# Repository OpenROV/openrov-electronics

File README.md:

<br>

<div align = center>

# OpenROV

***DIY Telerobotics*** for ***Underwater Exploration*** *&* ***Adventure*** *.*

<br>
<br>

[![Button Website]][Website]   
[![Button Forum]][Forum]   
[![Button BOM]][BOM]   
[![Button Hardware]][Hardware]

</div>

<br>
<br>

## Contents

This repository contains all files related<br>
to our **OpenROV DIY Kits**, these include <br>
`Schematics`, `Gerbers`, `Diagrams`, `..`

<br>
<br>

## Releases

<br>

-   **[`2.6`]**  |  **[`2.7`]**  |  **[`2.8`]**

    All-in-one power and control board that <br>
    has a Arduino based  `Atmega 2560`  board.
    
    Tons of I/O and designed to <br>
    fit the  `BeagleBone Black` .

    <br>

-   **[`2.5`]**

    All-in-one power & control board that has <br>
    a Arduino based  `Atmega 2560`  board.
    
    Tons of I/O and designed to fit both <br>
    `BeagleBone`  &  `BeagleBone Black` .

    <br>

-   **[`2.3`]**  |  **[`2.4`]**

    All-in-one power & control board <br>
    based around the  `Atmega 328` .

<br>

<!----------------------------------------------------------------------------->

[Hardware]: https://github.com/OpenROV/openrov-hardware
[Website]: http://openrov.com/
[Forum]: https://forum.openrov.com/
[BOM]: https://docs.google.com/spreadsheet/ccc?key=0Avf6fUwp9B3kdF9YQWxBTnZjZEVGZVQwY25EbnVyREE&usp=sharing

[`2.3`]: ./OpenROV%20BeagleBone%20Cape%20Rev%20A1%20v2.3%20v2.4
[`2.4`]: ./OpenROV%20BeagleBone%20Cape%20Rev%20A1%20v2.3%20v2.4
[`2.8`]: ./OpenROV%20Controller%202.8%20Final%20Data%20Pkg
[`2.7`]: ./OpenROV%20Controller%202.7%20Final%20Data%20Pkg
[`2.5`]: ./OpenROV%20Controller%202.5B
[`2.6`]: ./OpenROV%20Controller%202.6

<!---------------------------------[ Buttons ]--------------------------------->

[Button Hardware]: https://img.shields.io/badge/Hardware-81B441?style=for-the-badge&logoColor=white&logo=GodotEngine
[Button Website]: https://img.shields.io/badge/Website-1293D8?style=for-the-badge&logoColor=white&logo=GoogleChrome
[Button Forum]: https://img.shields.io/badge/Forum-782A90?style=for-the-badge&logoColor=white&logo=ElasticStack
[Button BOM]: https://img.shields.io/badge/Bill_Of_Material-E04E39?style=for-the-badge&logoColor=white&logo=Docs.rs

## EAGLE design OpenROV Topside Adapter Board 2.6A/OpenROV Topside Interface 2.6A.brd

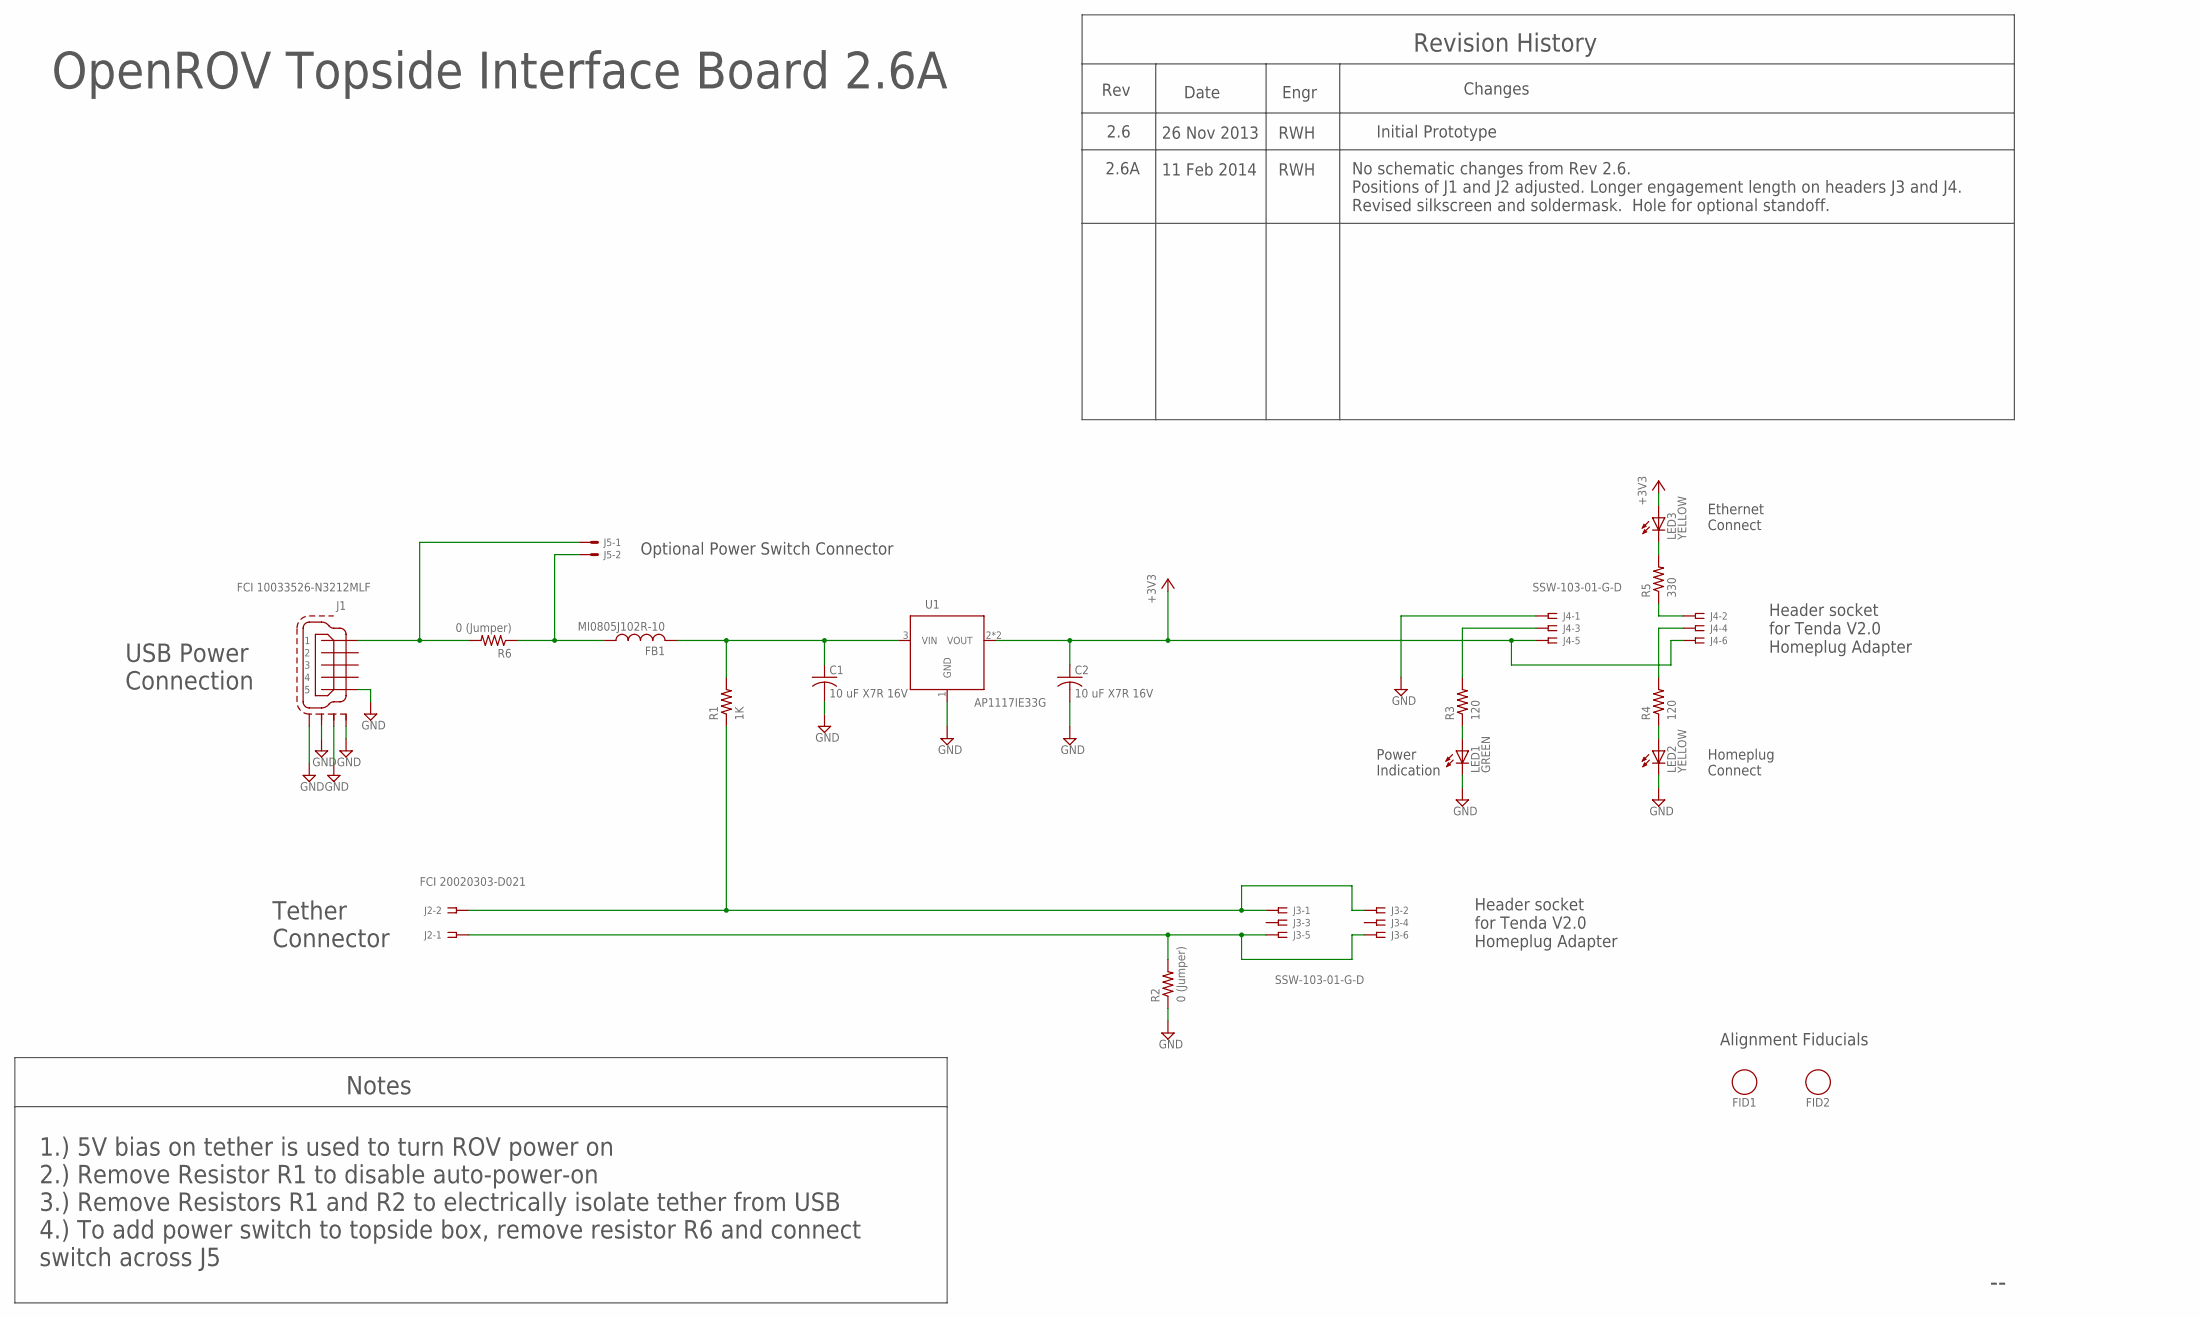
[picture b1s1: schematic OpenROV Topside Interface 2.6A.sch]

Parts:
C1, C2: 10 uF X7R 16V; R1206
FB1: MI0805J102R-10; R0805
FID1, FID2: FIDUCIAL_1
J1: FCI 10033526-N3212MLF; USB_MINI-B_SM
J2: FCI 20020303-D021; FCI_09-381_2PL
J3, J4: SSW-103-01-G-D; SSW-103-02-S-D
J5: HDR_1X2X0.100-ALT_SILK; 22-23-2021_ALT_SILK
LED1: GREEN; LED_0805_BOTTOM_MT(OSRAM)
LED2, LED3: YELLOW; LED_0805_BOTTOM_MT(OSRAM)
R1: 1K; R0805
R2, R6: 0 (Jumper); R0805
R3, R4: 120; R0805
R5: 330; R0805
U1: AP1117IE33G; SOT223

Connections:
+3V3: C2.1, J4.5, J4.6, LED3.A, U1.2 (VOUT), U1.4 (VOUT)
GND: C1.2, C2.2, J1.5, J1.M1 (S1), J1.M2 (S2), J1.M3 (S3), J1.M4 (S4), J4.1, LED1.C, LED2.C, R2.1, U1.1 (GND)
unnamed: J2.1A, J2.1B, J3.5, J3.6, R2.2
unnamed: J2.2A, J2.2B, J3.1, J3.2, R1.1
unnamed: J1.1, J5.1, R6.2
unnamed: C1.1, FB1.2, R1.2, U1.3 (VIN)
unnamed: LED3.C, R5.2
unnamed: J4.3, R3.2
unnamed: LED1.A, R3.1
unnamed: LED2.A, R4.1
unnamed: J4.4, R4.2
unnamed: FB1.1, J5.2, R6.1
unnamed: J4.2, R5.1

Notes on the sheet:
Revision History
Rev
Date
Changes
2.6
26 Nov 2013
Initial Prototype
Engr
RWH
OpenROV Topside Interface Board 2.6A
Tether Connector
USB Power Connection
Header socket for Tenda V2.0 Homeplug Adapter
Power Indication
Homeplug Connect
Ethernet Connect
Notes
1.) 5V bias on tether is used to turn ROV power on 2.) Remove Resistor R1 to disable auto-power-on 3.) Remove Resistors R1 and R2 to electrically isolate tether from USB 4.) To add power switch to topside box, remove resistor R6 and connect switch across J5
Alignment Fiducials
Optional Power Switch Connector
2.6A
11 Feb 2014
No schematic changes from Rev 2.6. Positions of J1 and J2 adjusted. Longer engagement length on headers J3 and J4. Revised silkscreen and soldermask. Hole for optional standoff.

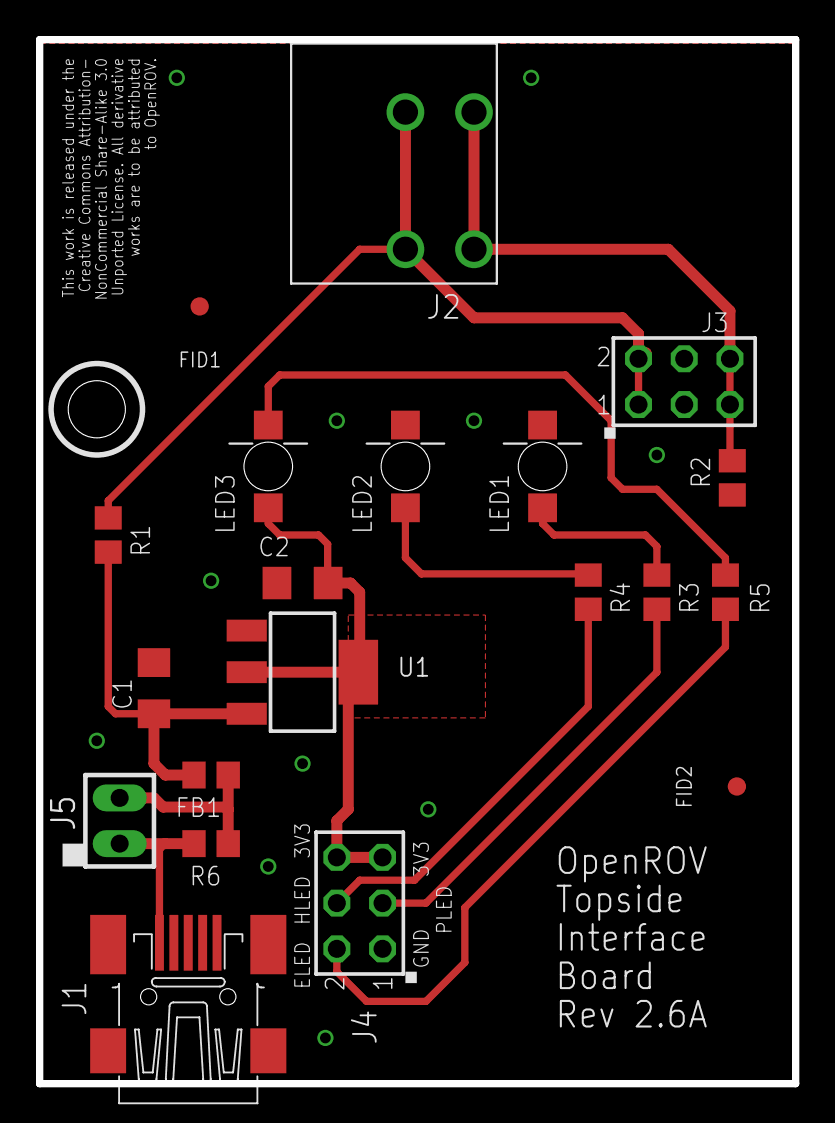
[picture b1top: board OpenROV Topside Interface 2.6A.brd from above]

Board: 4 copper layers, 42.0 x 58.0 mm, 20 parts (0 on the bottom side), 13 nets.

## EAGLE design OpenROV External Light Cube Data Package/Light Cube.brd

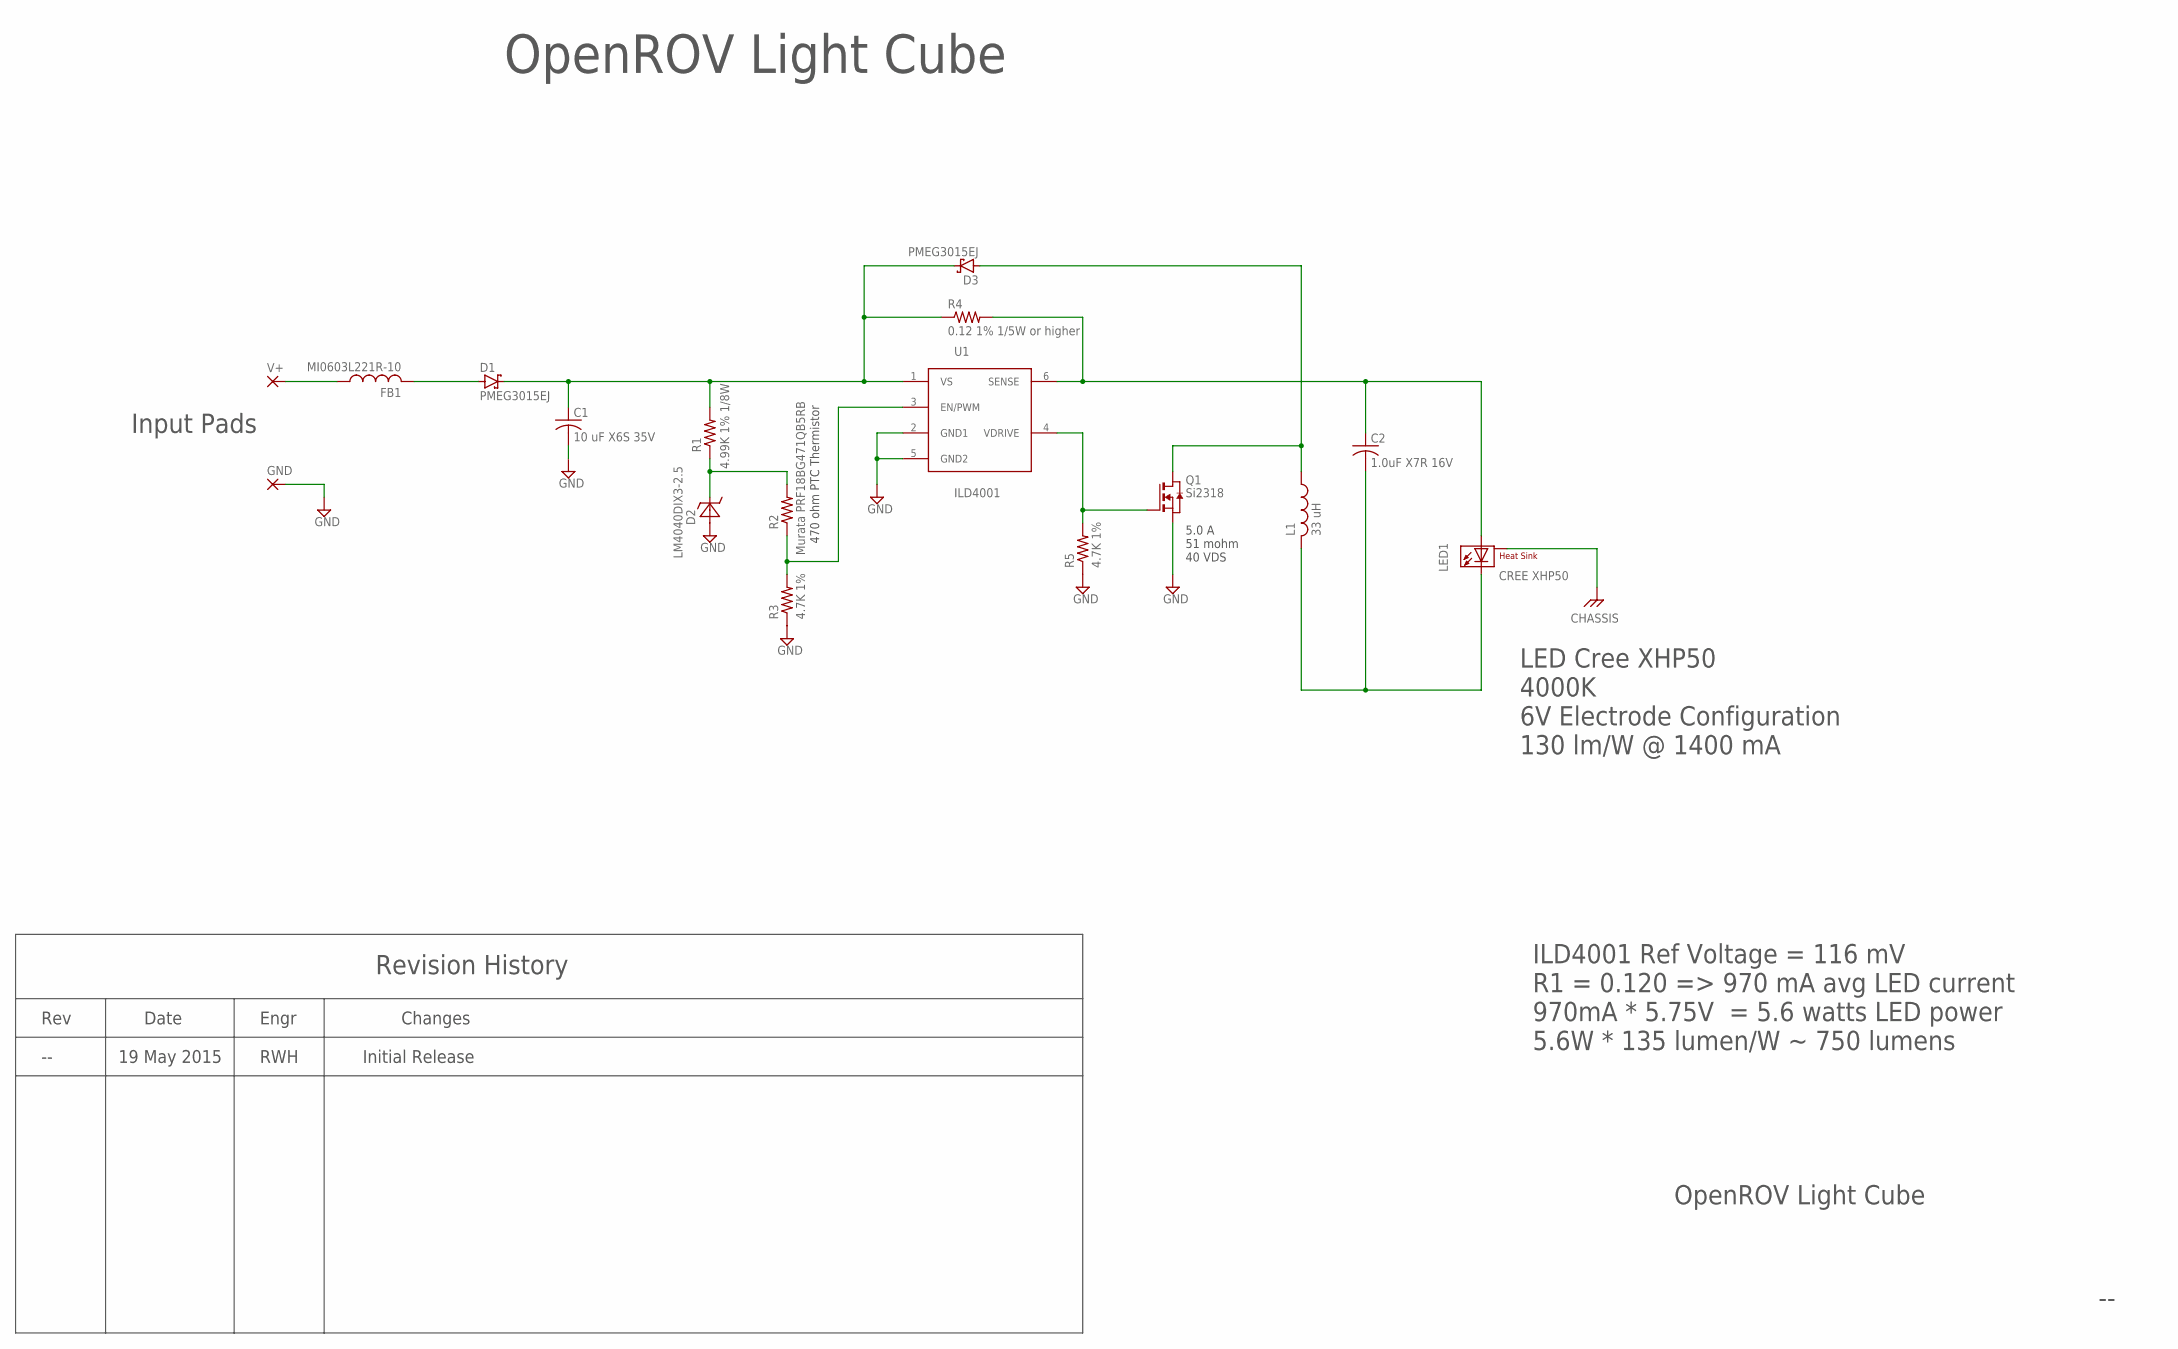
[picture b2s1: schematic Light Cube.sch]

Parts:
C1: 10 uF X6S 35V; R0805
C2: 1.0uF X7R 16V; R0603
D1, D3: PMEG3015EJ; SOD323
D2: LM4040DIX3-2.5; SC70-3
FB1: MI0603L221R-10; R0603
GND: SMD_PAD3/3; SMD_3_3
L1: 33 uH; INDUCTOR_LAIRD_TYS6045
LED1: CREE XHP50; CREE_XHP50_6V
Q1: Si2318; SOT23
R1: 4.99K 1% 1/8W; R0402
R2: Murata PRF18BG471QB5RB; R0603
R3, R5: 4.7K 1%; R0402
R4: 0.12 1% 1/5W or higher; R0603
U1: ILD4001; SC74_INFINEON
V+: SMD_PAD-2/2; SMD_2_2

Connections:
CHASSIS: LED1.SINK (HEATSINK)
GND: C1.2, D2.2 (A), GND.1, Q1.2 (S), R3.1, R5.1, U1.2 (GND1), U1.5 (GND2)
unnamed: D2.1 (C), R1.1, R2.2
unnamed: FB1.1, V+.1
unnamed: D1.A, FB1.2
unnamed: C1.1, D1.C, D3.C, R1.2, R4.1, U1.1 (VS)
unnamed: R2.1, R3.2, U1.3 (EN/PWM)
unnamed: C2.1, LED1.A, R4.2, U1.6 (SENSE)
unnamed: D3.A, L1.P$1 (1), Q1.3 (D)
unnamed: C2.2, L1.P$2 (2), LED1.C
unnamed: Q1.1 (G), R5.2, U1.4 (VDRIVE)

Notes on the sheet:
OpenROV Light Cube
ILD4001 Ref Voltage = 116 mV R1 = 0.120 => 970 mA avg LED current 970mA * 5.75V = 5.6 watts LED power 5.6W * 135 lumen/W ~ 750 lumens
LED Cree XHP50 4000K 6V Electrode Configuration 130 lm/W @ 1400 mA
5.0 A 51 mohm 40 VDS
Revision History
Rev
Date
Engr
Changes
19 May 2015
RWH
Initial Release
Input Pads
470 ohm PTC Thermistor

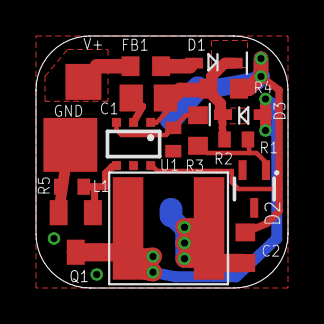
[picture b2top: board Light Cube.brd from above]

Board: 4 copper layers, 14.0 x 14.0 mm, 17 parts (1 on the bottom side), 10 nets.

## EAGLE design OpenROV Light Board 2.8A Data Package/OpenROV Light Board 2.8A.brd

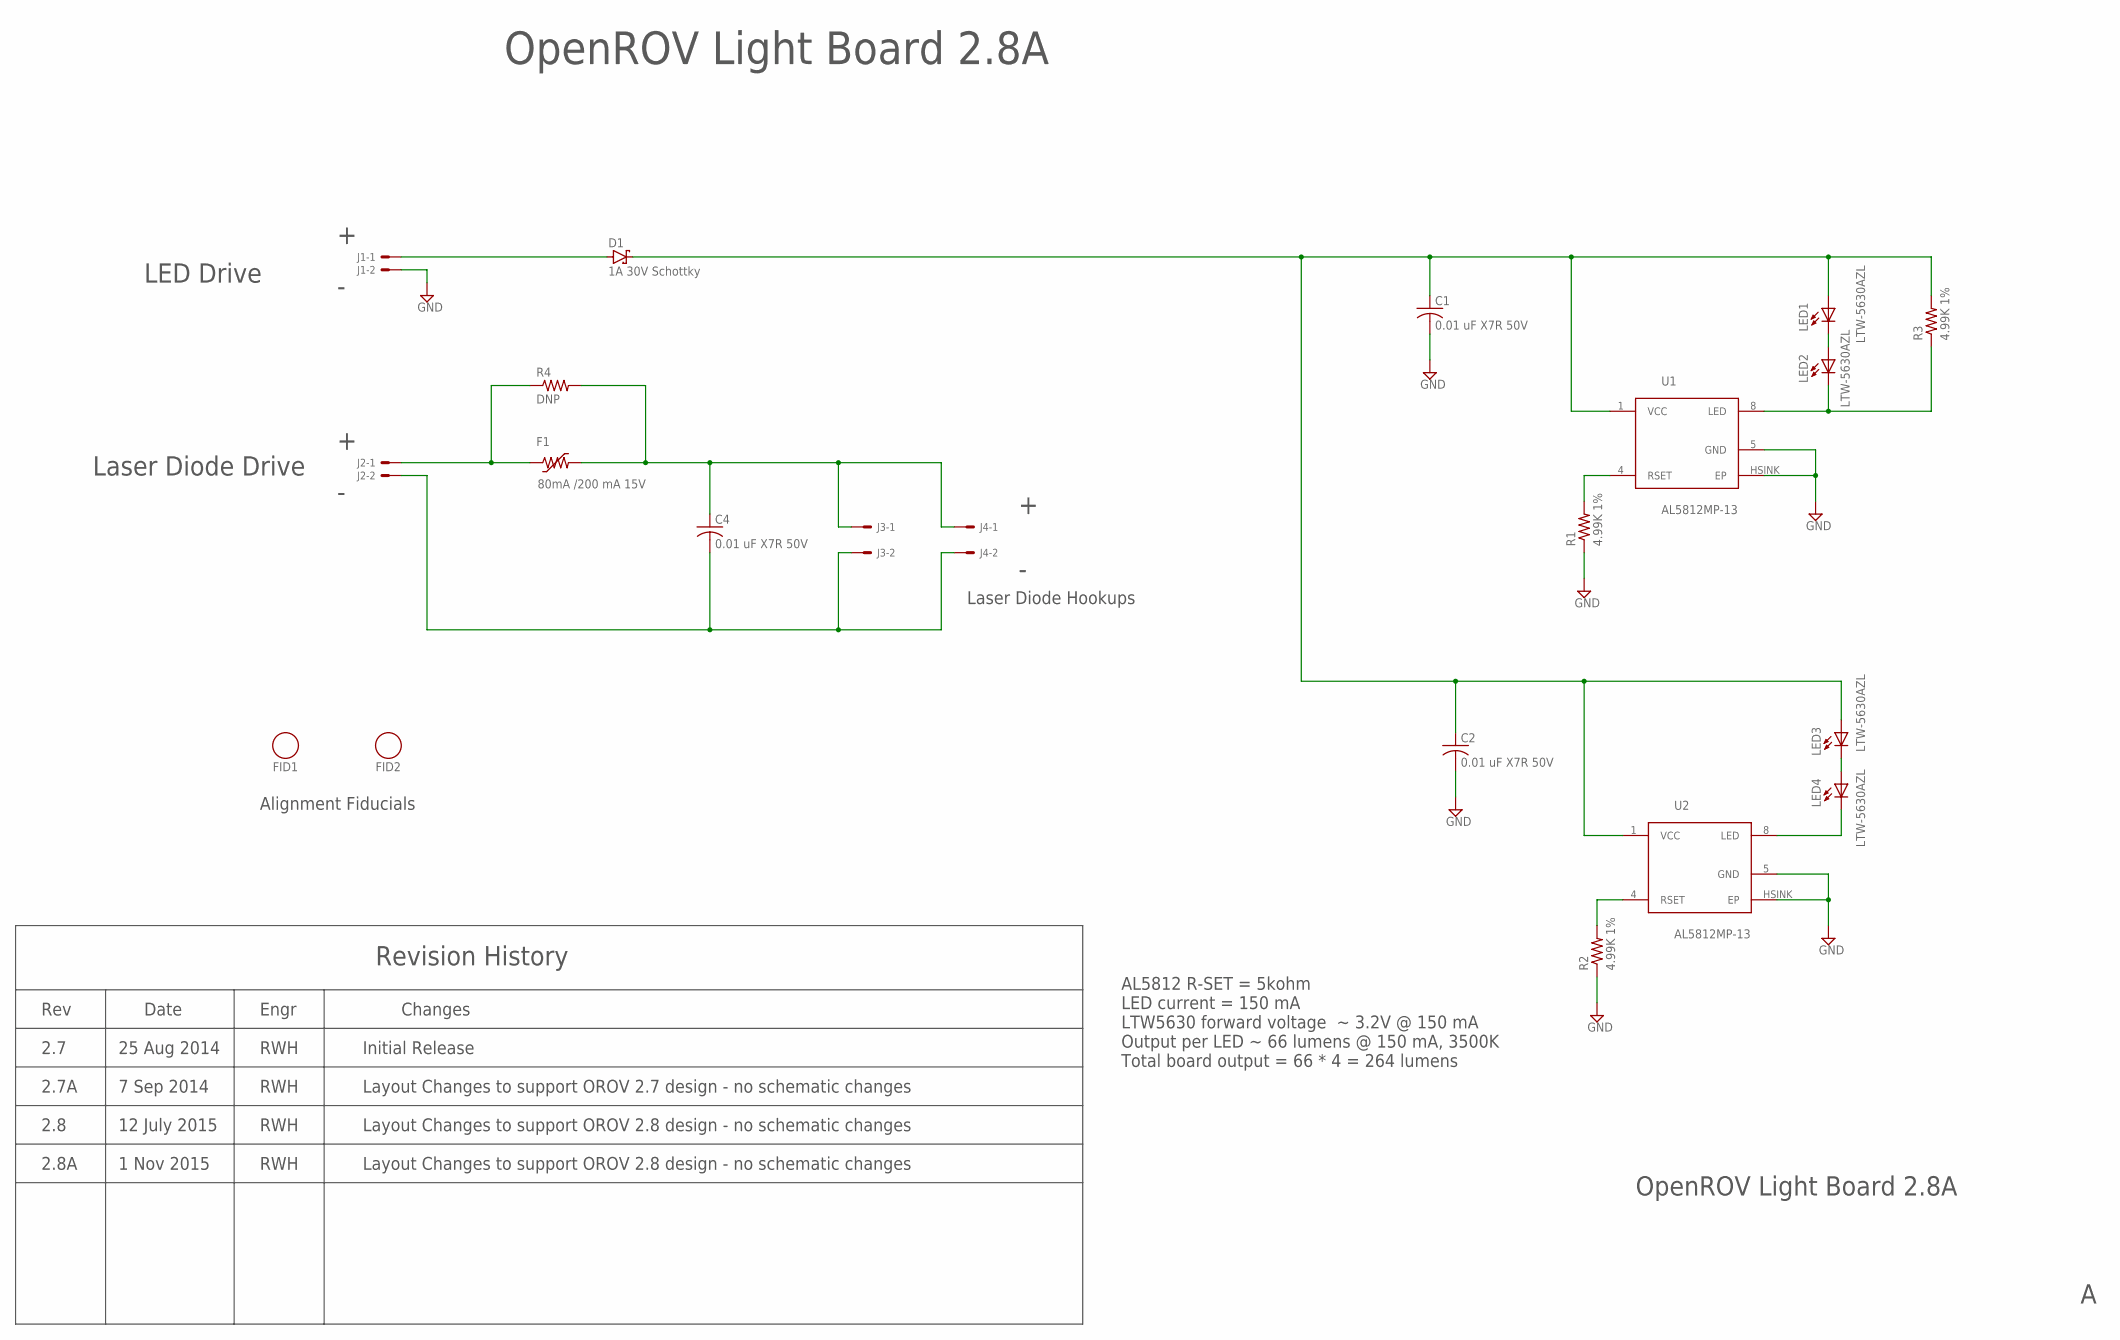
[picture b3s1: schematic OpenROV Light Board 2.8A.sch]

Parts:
C1, C2, C4: 0.01 uF X7R 50V; R0603
D1: 1A 30V Schottky; DO214AC
F1: 80mA /200 mA 15V; R0603
FID1, FID2: FIDUCIAL_1
J1, J2: SOLDER_PADS_3MM
J3, J4: SOLDER_PADS_3MM-SMALL_HOLE; SOLDER_PADS_3MM_SMALL_HOLE
LED1, LED2, LED3, LED4: LTW-5630AZL; LITEON-5630
R1, R2, R3: 4.99K 1%; R0603
R4: DNP; R1206
U1, U2: AL5812MP-13; MSOP-8EP

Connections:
GND: C1.2, C2.2, J1.2, R1.1, R2.1, U1.5 (GND), U1.HSINK (EP), U2.5 (GND), U2.HSINK (EP)
unnamed: LED2.C1 (C), LED2.C2 (C), R3.1, U1.8 (LED)
unnamed: LED1.C1 (C), LED1.C2 (C), LED2.A1 (A), LED2.A2 (A), LED2.A3 (A)
unnamed: C4.1, F1.2, J3.1, J4.1, R4.2
unnamed: C4.2, J2.2, J3.2, J4.2
unnamed: F1.1, J2.1, R4.1
unnamed: R1.2, U1.4 (RSET)
unnamed: LED4.C1 (C), LED4.C2 (C), U2.8 (LED)
unnamed: LED3.C1 (C), LED3.C2 (C), LED4.A1 (A), LED4.A2 (A), LED4.A3 (A)
unnamed: C1.1, C2.1, D1.C, LED1.A1 (A), LED1.A2 (A), LED1.A3 (A), LED3.A1 (A), LED3.A2 (A), LED3.A3 (A), R3.2, U1.1 (VCC), U2.1 (VCC)
unnamed: D1.A, J1.1
unnamed: R2.2, U2.4 (RSET)

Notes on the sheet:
OpenROV Light Board 2.8A
Laser Diode Drive
LED Drive
Laser Diode Hookups
Revision History
Rev
Date
Engr
Changes
2.7
25 Aug 2014
RWH
Initial Release
Alignment Fiducials
Layout Changes to support OROV 2.7 design - no schematic changes
7 Sep 2014
2.7A
2.8
12 July 2015
Layout Changes to support OROV 2.8 design - no schematic changes
AL5812 R-SET = 5kohm LED current = 150 mA LTW5630 forward voltage ~ 3.2V @ 150 mA Output per LED ~ 66 lumens @ 150 mA, 3500K Total board output = 66 * 4 = 264 lumens
2.8A
1 Nov 2015

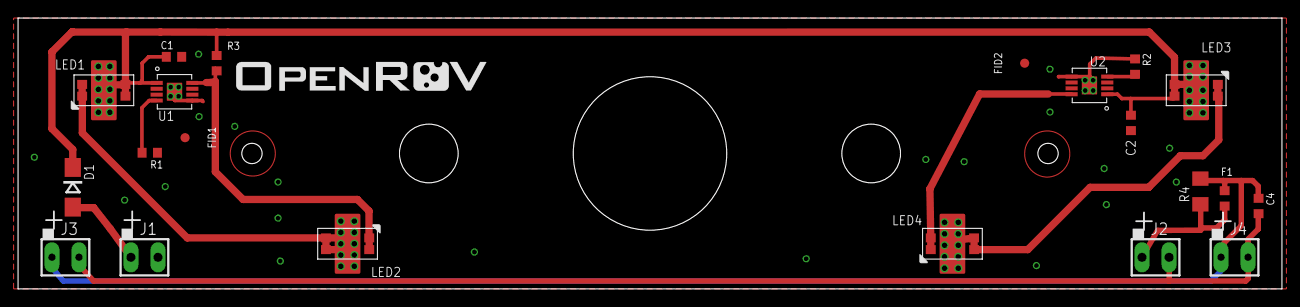
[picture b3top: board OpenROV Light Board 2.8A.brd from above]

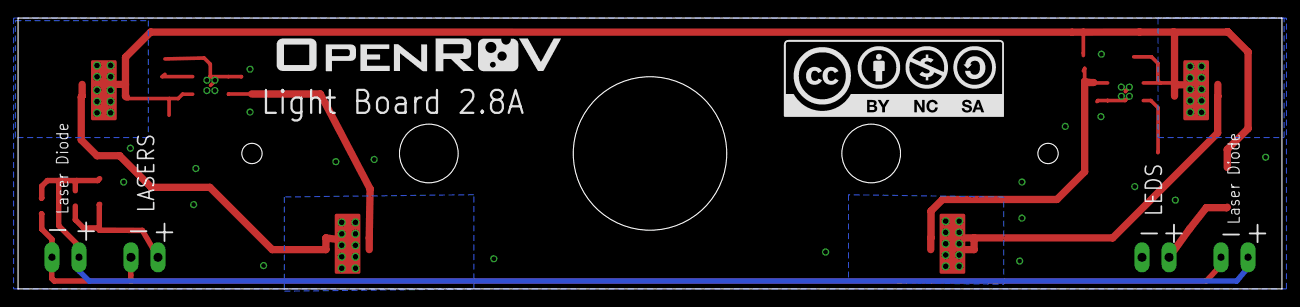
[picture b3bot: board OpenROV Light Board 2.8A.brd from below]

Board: 4 copper layers, 140.0 x 30.0 mm, 24 parts (2 on the bottom side), 12 nets.

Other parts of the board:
U$1: CC-LOGO-1-TOP
U$2: OROV-LOGO-1.25
U$4: OROV-LOGO-1.10

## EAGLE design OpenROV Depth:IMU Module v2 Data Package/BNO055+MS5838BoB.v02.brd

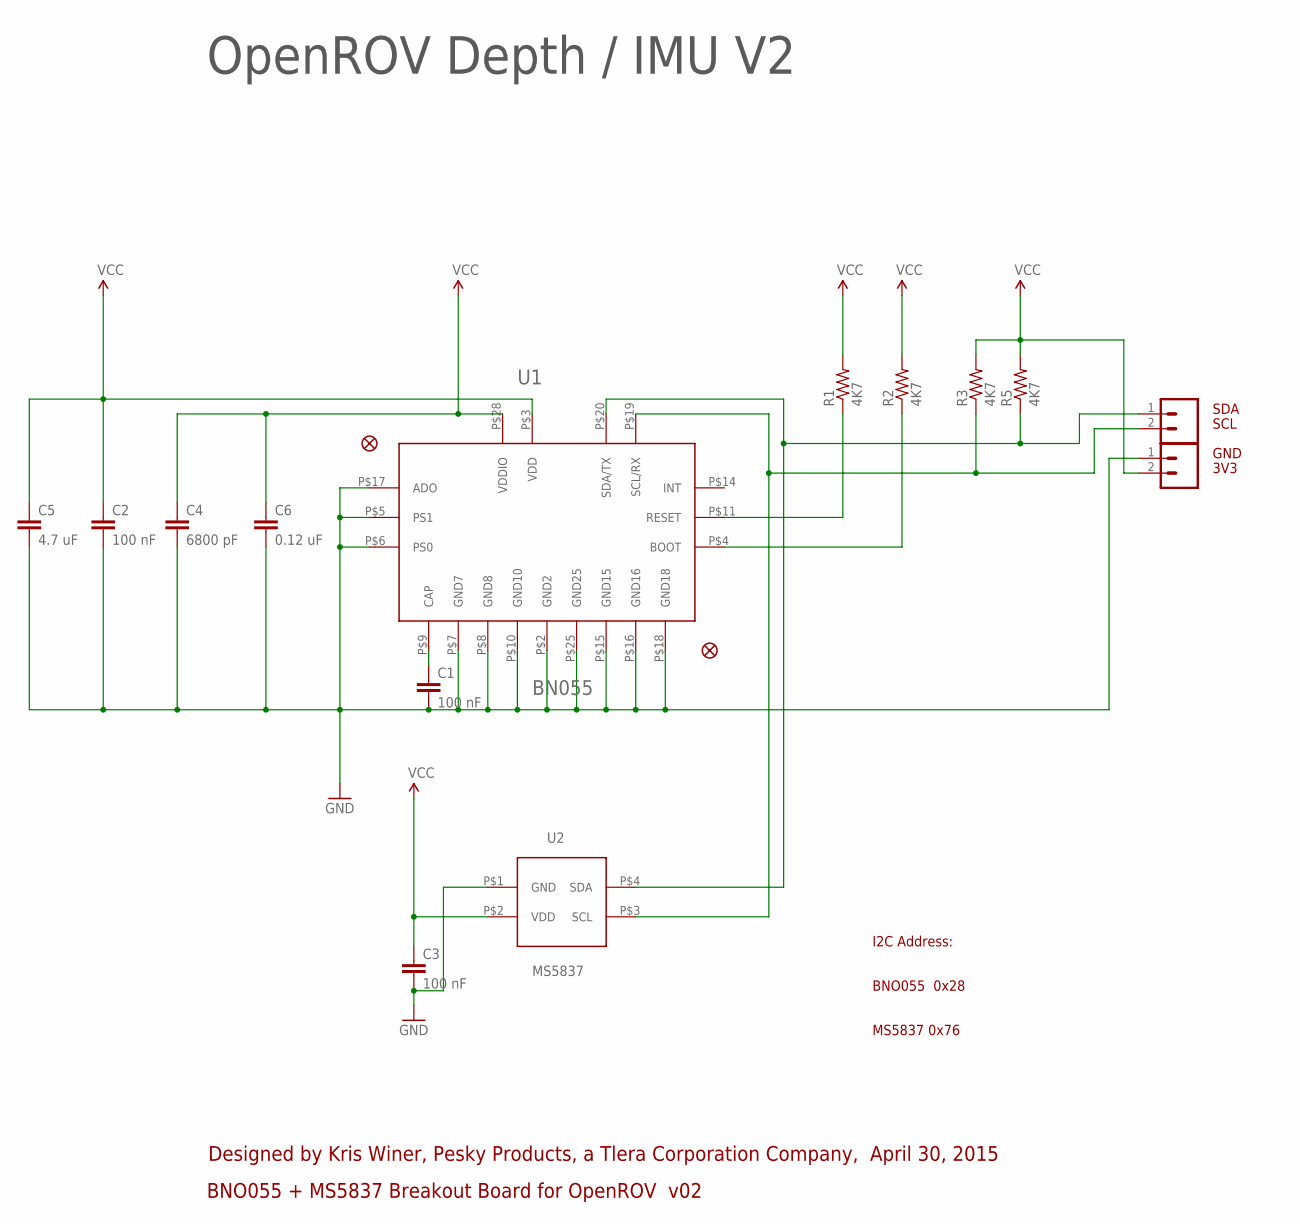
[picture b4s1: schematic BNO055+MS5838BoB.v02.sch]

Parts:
C1, C2, C3: 100 nF; C0402
C4: 6800 pF; C0402
C5: 4.7 uF; C0402
C6: 0.12 uF; C0402
FID1, FID2: FIDUCIALUFIDUCIAL; MICRO-FIDUCIAL
JP2, JP3: M021X02_NO_SILK; 1X02_NO_SILK
R1, R2, R3, R5: 4K7; R0402
U1: BN055; LGA28
U2: MS5837

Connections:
GND: C1.2, C2.2, C3.2, C4.2, C5.2, C6.2, JP3.1, U1.P$2 (GND2), U1.P$5 (PS1), U1.P$6 (PS0), U1.P$7 (GND7), U1.P$8 (GND8), U1.P$10 (GND10), U1.P$15 (GND15), U1.P$16 (GND16), U1.P$17 (ADO), U1.P$18 (GND18), U1.P$25 (GND25), U2.P$1 (GND)
unnamed: R1.1, U1.P$11 (RESET)
unnamed: C1.1, U1.P$9 (CAP)
unnamed: R2.1, U1.P$4 (BOOT)
SCL: JP2.2, R3.1, U1.P$19 (SCL/RX), U2.P$3 (SCL)
SDA: JP2.1, R5.1, U1.P$20 (SDA/TX), U2.P$4 (SDA)
VCC: C2.1, C3.1, C4.1, C5.1, C6.1, JP3.2, R1.2, R2.2, R3.2, R5.2, U1.P$3 (VDD), U1.P$28 (VDDIO), U2.P$2 (VDD)

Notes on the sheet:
Designed by Kris Winer, Pesky Products, a Tlera Corporation Company, April 30, 2015
BNO055 + MS5837 Breakout Board for OpenROV v02
SDA
SCL
GND
3V3
I2C Address:
BNO055 0x28
MS5837 0x76
OpenROV Depth / IMU V2

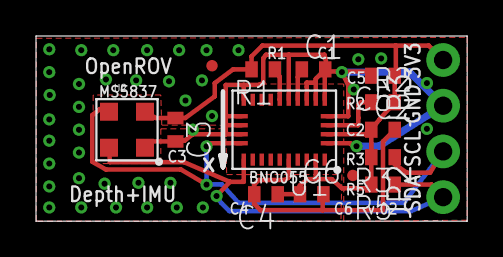
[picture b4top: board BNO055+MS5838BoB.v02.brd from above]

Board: 2 copper layers, 24.0 x 10.3 mm, 17 parts (1 on the bottom side), 7 nets.

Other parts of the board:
U$2: OROV-LOGO-0.500

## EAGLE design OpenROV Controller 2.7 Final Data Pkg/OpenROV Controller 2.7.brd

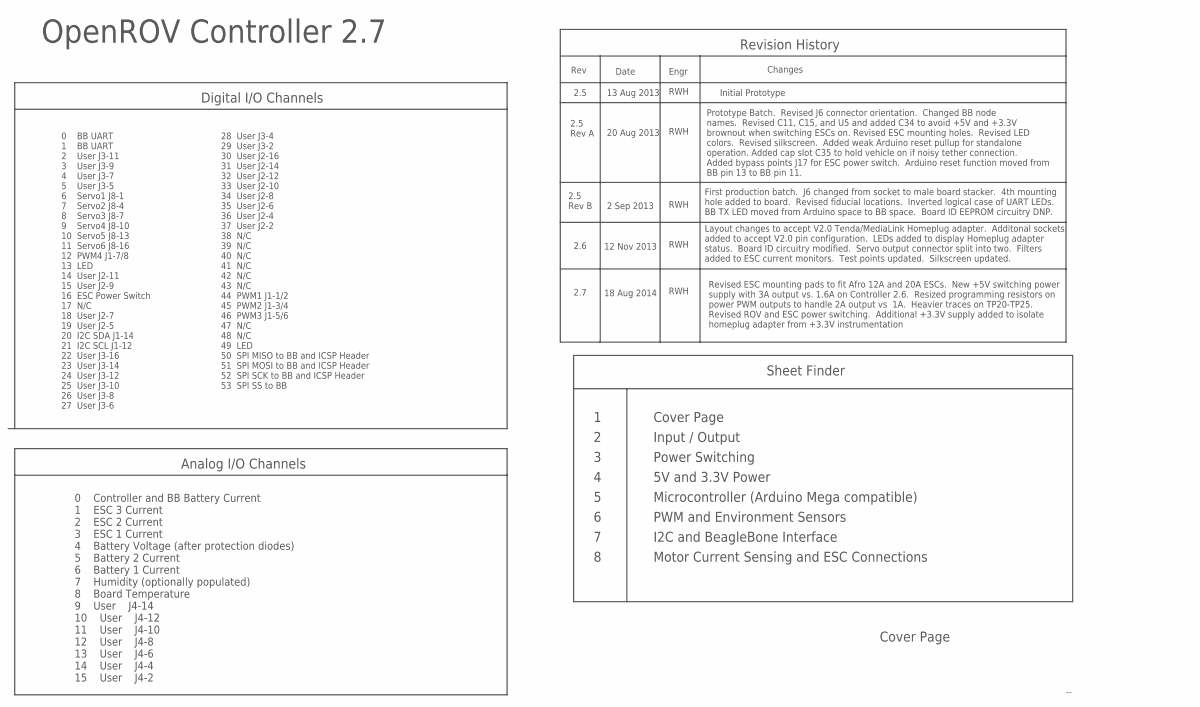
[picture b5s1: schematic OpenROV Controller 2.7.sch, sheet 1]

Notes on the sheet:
Revision History
Rev
Date
Changes
2.5
13 Aug 2013
Initial Prototype
Sheet Finder
Cover Page
Input / Output
Power Switching
5V and 3.3V Power
Microcontroller (Arduino Mega compatible)
PWM and Environment Sensors
I2C and BeagleBone Interface
OpenROV Controller 2.7
Analog I/O Channels
Digital I/O Channels
Motor Current Sensing and ESC Connections
0 Controller and BB Battery Current 1 ESC 3 Current 2 ESC 2 Current 3 ESC 1 Current 4 Battery Voltage (after protection diodes) 5 Battery 2 Current 6 Battery 1 Current 7 Humidity (optionally populated) 8 Board Temperature 9 User J4-14 10 User J4-12 11 User J4-10 12 User J4-8 13 User J4-6 14 User J4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
0 BB UART 1 BB UART 2 User J3-11 3 User J3-9 4 User J3-7 5 User J3-5 6 Servo1 J8-1 7 Servo2 J8-4 8 Servo3 J8-7 9 Servo4 J8-10 10 Servo5 J8-13 11 Servo6 J8-16 12 PWM4 J1-7/8 13 LED 14 User J2-11 15 User J2-9 16 ESC Power Switch 17 N/C 18 User J2-7 19 User J2-5 20 I2C SDA J1-14 21 I2C SCL J1-12 22 Us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
Engr
RWH
28 User J3-4 29 User J3-2 30 User J2-16 31 User J2-14 32 User J2-12 33 User J2-10 34 User J2-8 35 User J2-6 36 User J2-4 37 User J2-2 38 N/C 39 N/C 40 N/C 41 N/C 42 N/C 43 N/C 44 PWM1 J1-1/2 45 PWM2 J1-3/4 46 PWM3 J1-5/6 47 N/C 48 N/C 49 LED 50 SPI MISO to BB and ICSP Header 51 SPI MOSI to BB and I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
2.5 Rev A
20 Aug 2013
Prototype Batch. Revised J6 connector orientation. Changed BB node names. Revised C11, C15, and U5 and added C34 to avoid +5V and +3.3V brownout when switching ESCs on. Revised ESC mounting holes. Revised LED colors. Revised silkscreen. Added weak Arduino reset pullup for standalone operation. Adde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
2.5 Rev B
2 Sep 2013
First production batch. J6 changed from socket to male board stacker. 4th mounting hole added to board. Revised fiducial locations. Inverted logical case of UART LEDs. BB TX LED moved from Arduino space to BB space. Board ID EEPROM circuitry DNP.
2.6
12 Nov 2013
Layout changes to accept V2.0 Tenda/MediaLink Homeplug adapter. Additonal sockets added to accept V2.0 pin configuration. LEDs added to display Homeplug adapter status. Board ID circuitry modified. Servo output connector split into two. Filters added to ESC current monitors. Test points updated. Si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
2.7
18 Aug 2014
Revised ESC mounting pads to fit Afro 12A and 20A ESCs. New +5V switching power supply with 3A output vs. 1.6A on Controller 2.6. Resized programming resistors on power PWM outputs to handle 2A output vs 1A. Heavier traces on TP20-TP25. Revised ROV and ESC power switching. Additional +3.3V supply a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

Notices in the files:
OpenROV Power Controller 2.1/Power Controller 2.1.brd:
Released under the Creative Commons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
parts and their libraries:
OpenROV General Library: This work is released under the Creative Commons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
SparkFun-Connectors: Licensing: CC v3.0 Share-Alike You are welcome to use this library for commercial purposes.
